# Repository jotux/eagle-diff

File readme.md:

## What is this?
This simple python script lets you visually diff eagle CAD schematic and board files.

## Install
 - Download eagle-dif.py somehwere on your path
 - Adjust eagle_path variable if it is different

## Prerequisites
 - PIL

## Git Setup
### Add this to your .gitconfig:

    [diff "eagle"]

        command = eagle-diff

### Add a .gitattributes file to your project with these lines:

    *.sch diff=eagle
    *.brd diff=eagle

## Try it out
### Clone this project then:
    git diff v1 v2 main.brd

## Example
### Schematic

### Board

## Contribute
Feel free to send pull requests with fixes/upgrades/whatever.

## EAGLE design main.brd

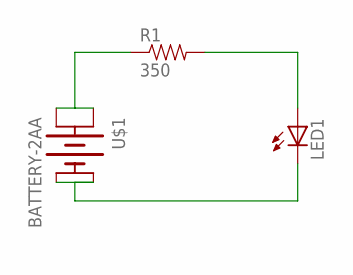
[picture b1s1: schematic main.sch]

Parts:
LED1: LED5MM
R1: 350; 1206
U$1: BATTERY-2AA; BATTERY-AA

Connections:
unnamed: R1.1, U$1.PWR@1 (+1), U$1.PWR@2 (+2)
unnamed: LED1.A, R1.2
unnamed: LED1.K (C), U$1.GND@1 (-1), U$1.GND@2 (-2)

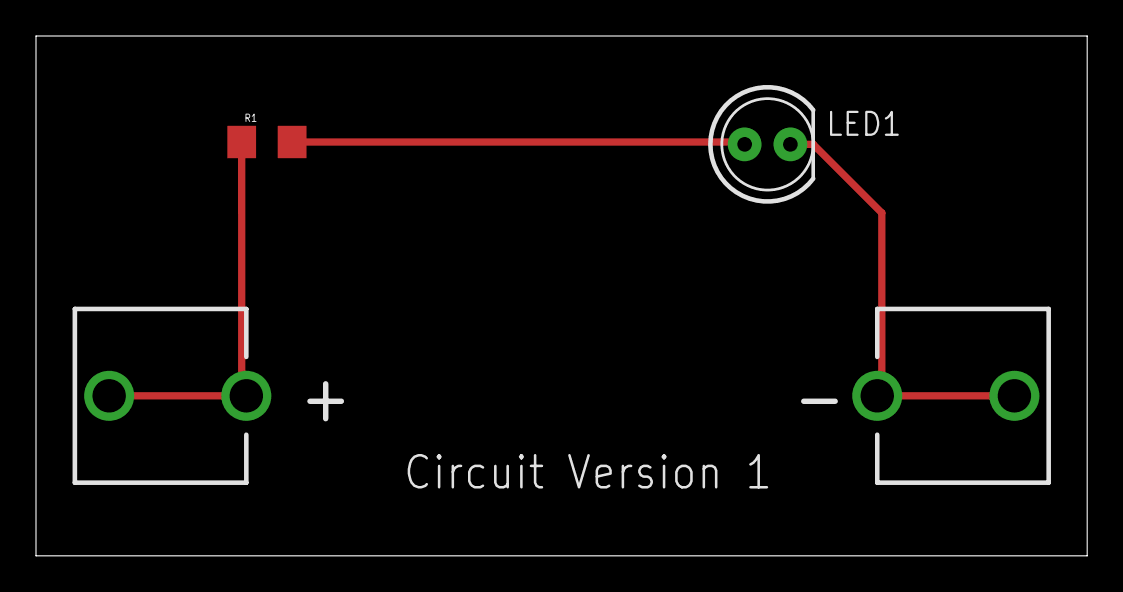
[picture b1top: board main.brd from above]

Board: 2 copper layers, 58.4 x 28.9 mm, 3 parts (0 on the bottom side), 3 nets.

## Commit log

2012-04-27 Add script and readme
2012-04-27 Fix readme command. Add pictures of examples
2012-04-27 Add image with more info.
2012-04-27 Note the script name in install instructions.
2012-04-27 Readme wording.
2012-04-27 Add intro section.
2012-09-04 Add schematic example image to readme.
